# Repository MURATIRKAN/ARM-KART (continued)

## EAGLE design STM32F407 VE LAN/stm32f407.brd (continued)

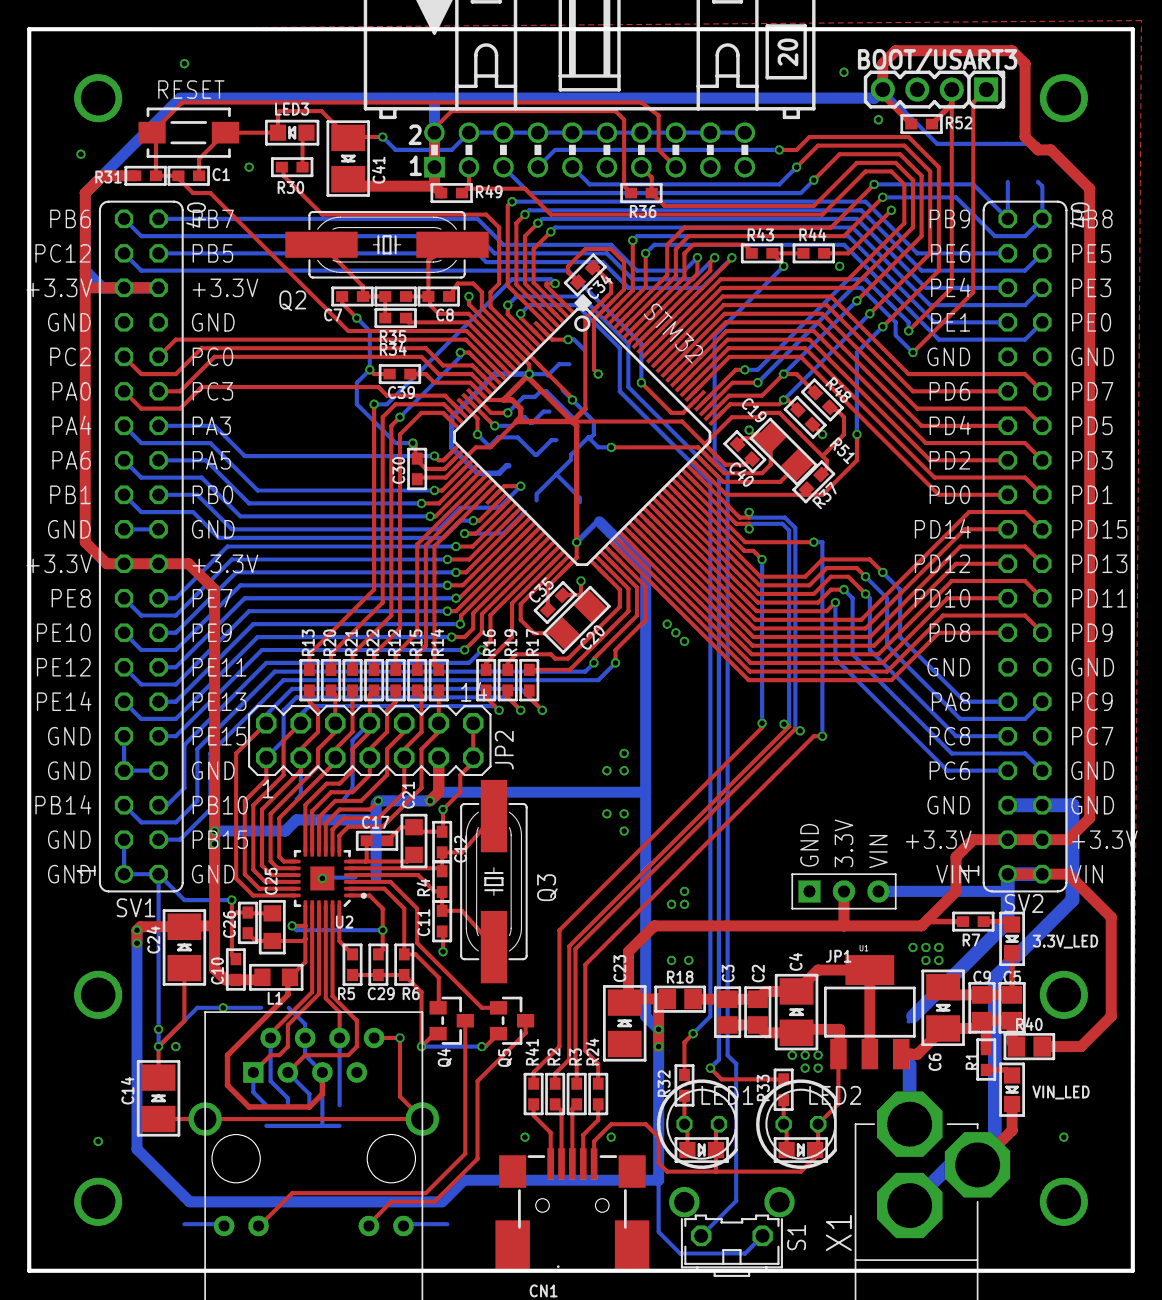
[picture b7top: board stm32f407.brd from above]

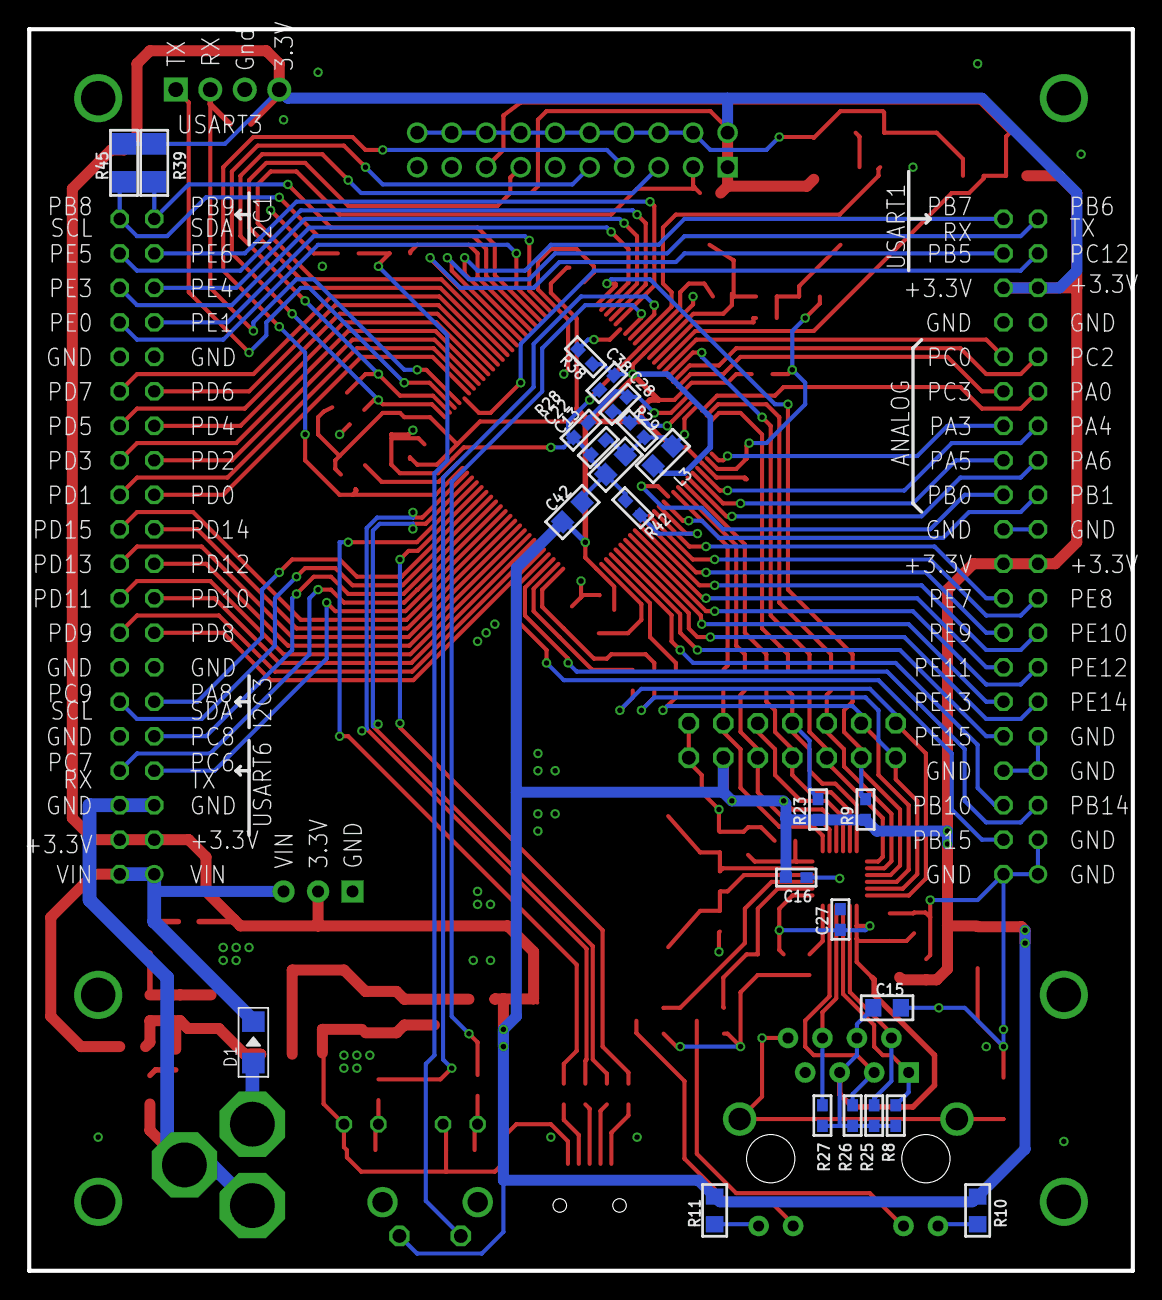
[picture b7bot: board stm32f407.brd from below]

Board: 4 copper layers, 81.3 x 91.4 mm, 119 parts (24 on the bottom side), 134 nets.

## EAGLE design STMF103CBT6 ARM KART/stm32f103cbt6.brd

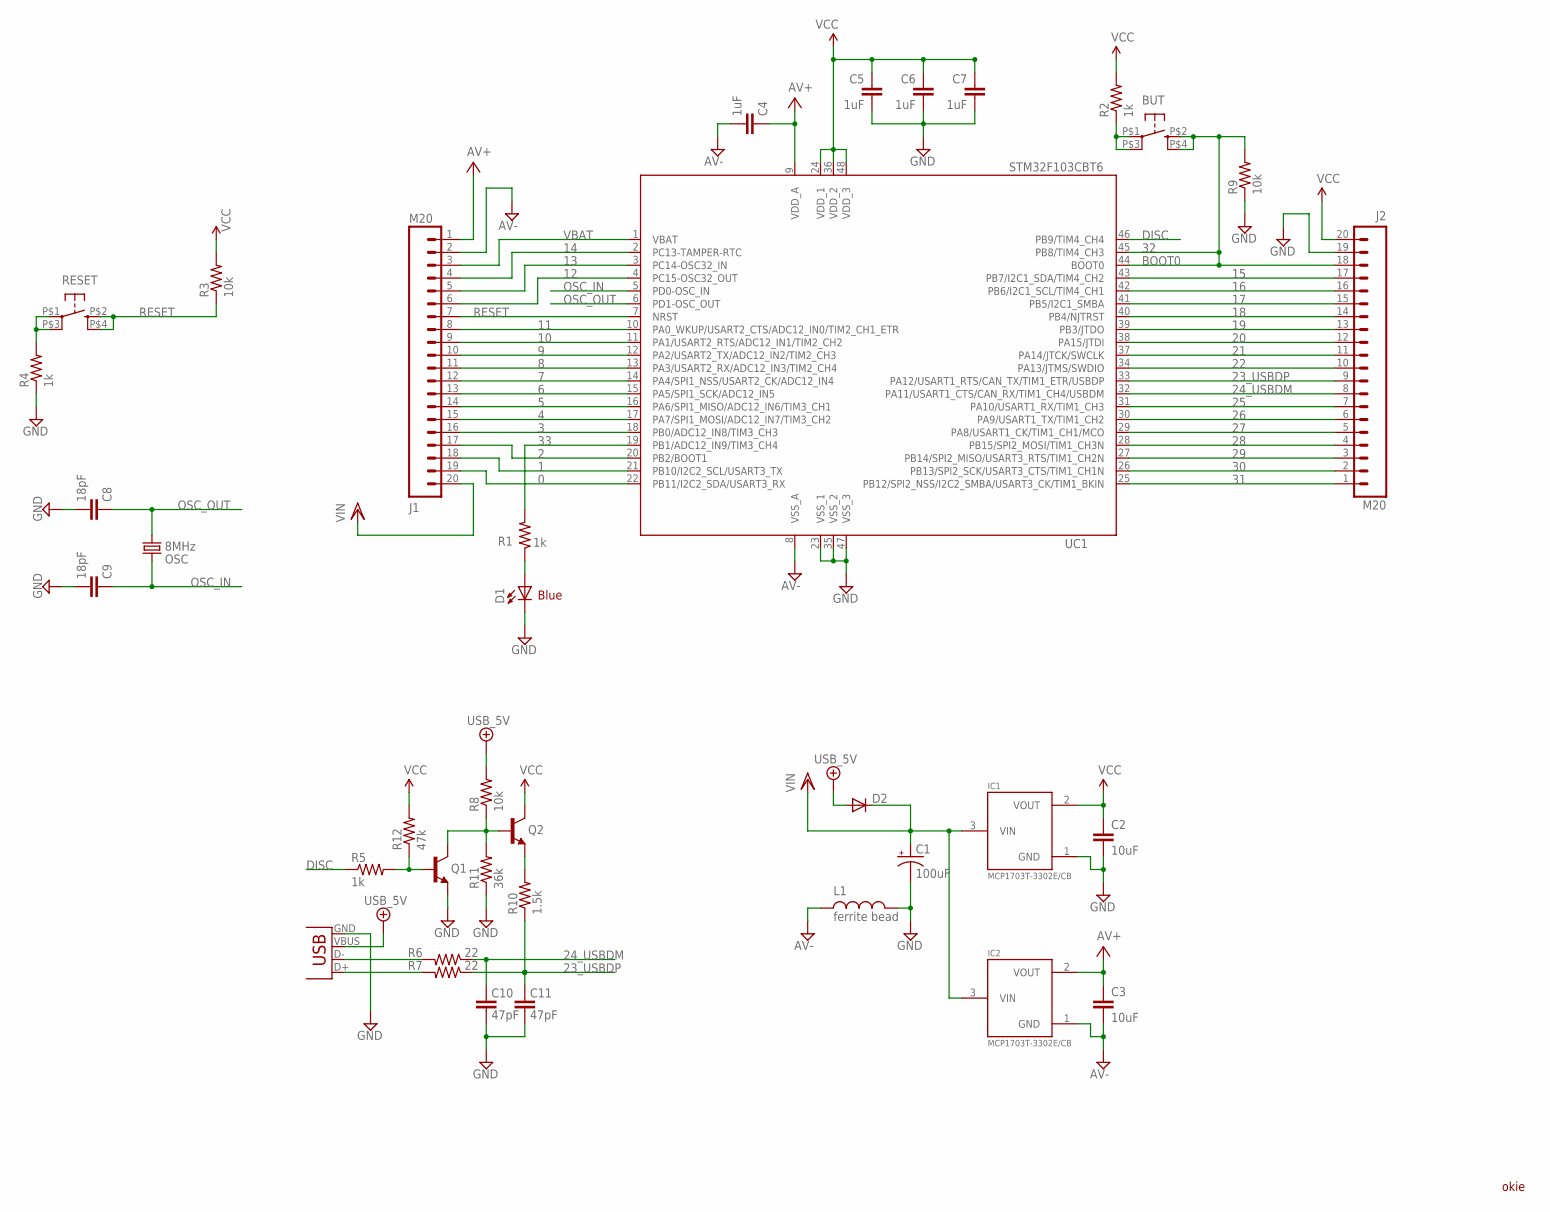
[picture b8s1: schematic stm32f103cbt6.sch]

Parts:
BUT: KMR211GLFS; PUSHBUTTON-KMR241GLFS
C1: 100uF; EIA3216
C2, C3: 10uF; 0805
C4, C5, C6, C7: 1uF; C0402
C8, C9: 18pF; C0402
C10, C11: 47pF; C0402
D1: Blue; LED-1206
D2: DIODESOD; SOD-323
IC1, IC2: MCP1703T-3302E/CB; SOT23
J1, J2: M20; 1X20
L1: ferrite bead; 0603
OSC: 8MHz; CRYSTAL-SMD-5X3
Q1, Q2: NPN-BJT; SOT23
R1, R2, R4, R5: 1k; C0402
R3, R8, R9: 10k; C0402
R6, R7: 22; C0402
R10: 1.5k; C0402
R11: 36k; C0402
R12: 47k; C0402
RESET: KMR211GLFS; PUSHBUTTON-KMR241GLFS
UC1: STM32F103CBT6; LQFP48
X1: USB-MINIB

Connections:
0: J1.19, UC1.22 (PB11/I2C2_SDA/USART3_RX)
1: J1.18, UC1.21 (PB10/I2C2_SCL/USART3_TX)
2: J1.17, UC1.20 (PB2/BOOT1)
3: J1.16, UC1.18 (PB0/ADC12_IN8/TIM3_CH3)
4: J1.15, UC1.17 (PA7/SPI1_MOSI/ADC12_IN7/TIM3_CH2)
5: J1.14, UC1.16 (PA6/SPI1_MISO/ADC12_IN6/TIM3_CH1)
6: J1.13, UC1.15 (PA5/SPI1_SCK/ADC12_IN5)
7: J1.12, UC1.14 (PA4/SPI1_NSS/USART2_CK/ADC12_IN4)
8: J1.11, UC1.13 (PA3/USART2_RX/ADC12_IN3/TIM2_CH4)
9: J1.10, UC1.12 (PA2/USART2_TX/ADC12_IN2/TIM2_CH3)
10: J1.9, UC1.11 (PA1/USART2_RTS/ADC12_IN1/TIM2_CH2)
11: J1.8, UC1.10 (PA0_WKUP/USART2_CTS/ADC12_IN0/TIM2_CH1_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)
12: J1.6, UC1.4 (PC15-OSC32_OUT)
13: J1.5, UC1.3 (PC14-OSC32_IN)
14: J1.4, UC1.2 (PC13-TAMPER-RTC)
15: J2.17, UC1.43 (PB7/I2C1_SDA/TIM4_CH2)
16: J2.16, UC1.42 (PB6/I2C1_SCL/TIM4_CH1)
17: J2.15, UC1.41 (PB5/I2C1_SMBA)
18: J2.14, UC1.40 (PB4/NJTRST)
19: J2.13, UC1.39 (PB3/JTDO)
20: J2.12, UC1.38 (PA15/JTDI)
21: J2.11, UC1.37 (PA14/JTCK/SWCLK)
22: J2.10, UC1.34 (PA13/JTMS/SWDIO)
23_USBDP: C11.2, J2.9, R7.1, R10.1, UC1.33 (PA12/USART1_RTS/CAN_TX/TIM1_ETR/USBDP)
24_USBDM: C10.2, J2.8, R6.1, UC1.32 (PA11/USART1_CTS/CAN_RX/TIM1_CH4/USBDM)
25: J2.7, UC1.31 (PA10/USART1_RX/TIM1_CH3)
26: J2.6, UC1.30 (PA9/USART1_TX/TIM1_CH2)
27: J2.5, UC1.29 (PA8/USART1_CK/TIM1_CH1/MCO)
28: J2.4, UC1.28 (PB15/SPI2_MOSI/TIM1_CH3N)
29: J2.3, UC1.27 (PB14/SPI2_MISO/USART3_RTS/TIM1_CH2N)
30: J2.2, UC1.26 (PB13/SPI2_SCK/USART3_CTS/TIM1_CH1N)
31: J2.1, UC1.25 (PB12/SPI2_NSS/I2C2_SMBA/USART3_CK/TIM1_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)
32: BUT.P$2 (2), BUT.P$4 (4), J2.18, R9.2, UC1.44 (BOOT0), UC1.45 (PB8/TIM4_CH3)
33: R1.2, UC1.19 (PB1/ADC12_IN9/TIM3_CH4)
+5V/2: D2.2 (A), R8.2, X1.VBUS
AV+: C3.1, C4.1, IC2.2 (VOUT), J1.1, UC1.9 (VDD_A)
AV-: C3.2, C4.2, IC2.1 (GND), J1.2, L1.1, UC1.8 (VSS_A)
DGND: C1.C (-), C2.2, C5.2, C6.2, C7.2, C8.2, C9.2, C10.1, C11.1, D1.C, IC1.1 (GND), J2.19, L1.2, Q1.2 (E), R4.1, R9.1, R11.1, UC1.23 (VSS_1), UC1.35 (VSS_2), UC1.47 (VSS_3), X1.GND
DISC: R5.1, UC1.46 (PB9/TIM4_CH4)
unnamed: BUT.P$1 (1), BUT.P$3 (3), R2.1
unnamed: D1.A, R1.1
unnamed: R4.2, RESET.P$1 (1), RESET.P$3 (3)
unnamed: Q2.2 (E), R10.2
unnamed: R6.2, X1.D-
unnamed: R7.2, X1.D+
unnamed: Q1.3 (C), Q2.1 (B), R8.1, R11.2
unnamed: Q1.1 (B), R5.2, R12.1
OSC_IN: C9.1, OSC.3 (2), UC1.5 (PD0-OSC_IN)
OSC_OUT: C8.1, OSC.1, UC1.6 (PD1-OSC_OUT)
RESET: J1.7, R3.1, RESET.P$2 (2), RESET.P$4 (4), UC1.7 (NRST)
VBAT: J1.3, UC1.1 (VBAT)
VCC: C2.1, C5.1, C6.1, C7.1, IC1.2 (VOUT), J2.20, Q2.3 (C), R2.2, R3.2, R12.2, UC1.24 (VDD_1), UC1.36 (VDD_2), UC1.48 (VDD_3)
VIN: C1.A (+), D2.1 (C), IC1.3 (VIN), IC2.3 (VIN), J1.20

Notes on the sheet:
okie
BOOT0
Blue

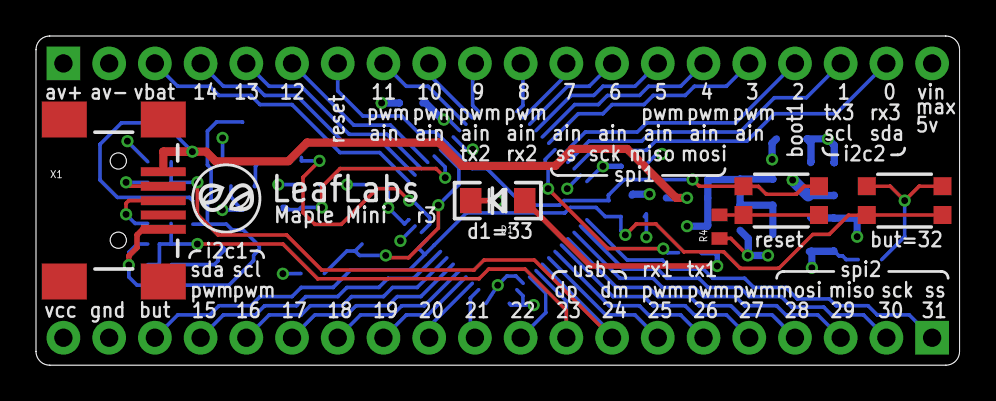
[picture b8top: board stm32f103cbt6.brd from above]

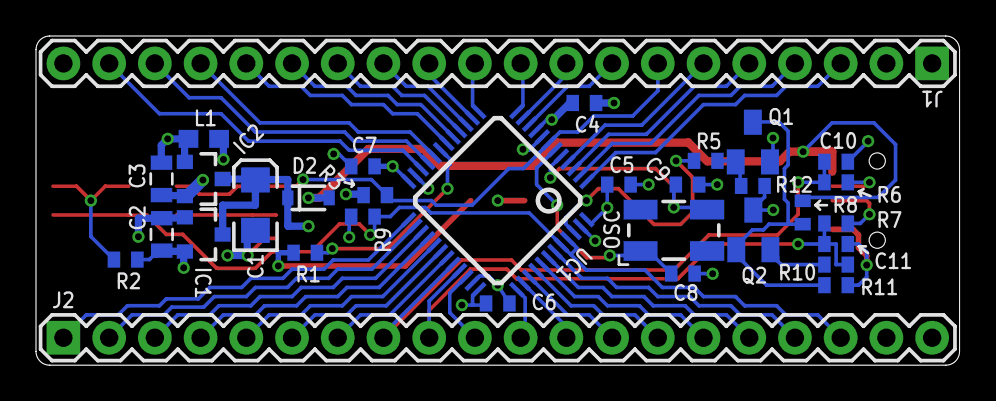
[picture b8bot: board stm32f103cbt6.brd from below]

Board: 2 copper layers, 51.3 x 18.3 mm, 37 parts (32 on the bottom side), 53 nets.

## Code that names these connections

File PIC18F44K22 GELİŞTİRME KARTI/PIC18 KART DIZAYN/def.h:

#ifndef INC_DEF_H
#define INC_DEF_H

#include <p18f44k22.h>
#include <delays.h>
#include <string.h>
#include <stdlib.h>
#include <stdio.h>
#include "init_periph.h"
#include "usart.h"
#include "analog.h"

//////////////////////////////////////////////////////////////////////////////////////////////
//                                                                                          //
//                                  		Prototypes                                		//
//                                                                                          //
//////////////////////////////////////////////////////////////////////////////////////////////

void pre_config(void);
void config(void);
void Interrupt_High(void); 
//void can_proc_message(CAN_MESSAGE *message);
//void init_default_variables(void);

//////////////////////////////////////////////////////////////////////////////////////////////
//                                                                                          //
//                                          Definitions                                     //
//                                                                                          //
//////////////////////////////////////////////////////////////////////////////////////////////

#define ANALOG_CHANNELS 12

//Inputs and outputs

//Analog (user)
#define TRIS_AN0	TRISAbits.TRISA0
#define TRIS_AN1	TRISAbits.TRISA1
#define TRIS_AN2	TRISAbits.TRISA2
#define TRIS_AN3	TRISAbits.TRISA3
#define TRIS_AN4	TRISAbits.TRISA5
#define TRIS_AN5	TRISEbits.TRISE0
#define TRIS_AN6	TRISEbits.TRISE1
#define TRIS_AN7	TRISEbits.TRISE2

//Digital (user)
#define DIO			PORTD
#define TRIS_DIO	TRISD
#define DIO_0		PORTDbits.RD0
#define TRIS_DIO_0	TRISDbits.TRISD0
#define DIO_1		PORTDbits.RD1
#define TRIS_DIO_1	TRISDbits.TRISD1
#define DIO_2		PORTDbits.RD2
#define TRIS_DIO_2	TRISDbits.TRISD2
#define DIO_3		PORTDbits.RD3
#define TRIS_DIO_3	TRISDbits.TRISD3
#define DIO_4		PORTDbits.RD4
#define TRIS_DIO_4	TRISDbits.TRISD4
#define DIO_5		PORTDbits.RD5
#define TRIS_DIO_5	TRISDbits.TRISD5
#define DIO_6		PORTDbits.RD6
#define TRIS_DIO_6	TRISDbits.TRISD6
#define DIO_7		PORTDbits.RD7
#define TRIS_DIO_7	TRISDbits.TRISD7

//Power outputs (user)
#define PWR_0		PORTCbits.RC0
#define TRIS_PWR_0	TRISCbits.TRISC0
#define PWR_1		PORTCbits.RC1
#define TRIS_PWR_1	TRISCbits.TRISC1
#define PWR_2		PORTCbits.RC2
#define TRIS_PWR_2	TRISCbits.TRISC2
#define PWR_3		PORTCbits.RC3
#define TRIS_PWR_3	TRISCbits.TRISC3
#define PWR_4		PORTCbits.RC4
#define TRIS_PWR_4	TRISCbits.TRISC4
#define PWR_5		PORTCbits.RC5
#define TRIS_PWR_5	TRISCbits.TRISC5

//Analog (pre-defined)
#define TRIS_TEMP	TRISBbits.TRISB1
#define TRIS_AMP	TRISBbits.TRISB2
#define TRIS_VOLT1	TRISBbits.TRISB3
#define TRIS_VOLT2	TRISBbits.TRISB4

//Misc.
#define ALIVE		LATAbits.LATA4
#define TRIS_ALIVE	TRISAbits.TRISA4
#define TRIS_RX		TRISCbits.TRISC7
#define TRIS_TX		TRISCbits.TRISC6

#endif

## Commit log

2022-09-24 STM32F401CCT6 ARM KART DİZAYN
    PCB VE ŞEMA.
    KİCAD ELEKTRONIK TASARIM PROGRAMI.
    https://www.kicad.org/
2022-09-24 STM32F042x6 ARM TEMEL KARTI
    NOT:KART PINLERI DEGISTIRILDI.!
2022-09-24 STM32F407 ARM GELISTIRME VE INTERNET KARTI
2022-09-24 STM32F042x6 SERİSİ DEMO KART DİZAYN.
    v.1.01
2022-09-26 STM32F405RGT6 ARM KART
2022-09-28 STM32F765VIT6 EAGLE VE DIP TRACE
    TASARLANIRKEN EAGLE TASARIM PROGRAMI VE DIP TRACE PROGRAMLARI KULLANILDI.
    1.https://diptrace.com/tr/
    2.https://www.autodesk.com/products/eagle/free-download
2022-09-29 STM32F401 ARM KEIL KOD
    ARM KEIL 6.18 DERLEYICI KULLANILDI.
2022-10-01 STM32F765VIT ARM KART V.1.02
    GUNCELLEME 9/1/2022
2022-10-02 STMF103CBT6 MINI ARM GELISTIRME KARTI
2022-10-02 stm32f103cbt6 pcb
2022-10-02 STM32F103 ZAMANLAMA VE LED KONTROL
    DERLEYICI KEIL ARM 6.18.
2022-10-08 STM32F103CBT6 TEMEL ARM KART
    ST MICROELEKTRONICS STM32F103CBT6 ARM - CORTEX M3 İŞLEMCİ
2022-10-08 STM32F103 ARM KEIL 6.18 DERLEYİCİ.
    STM32F103 ZAMANLAMA TEST KOD..
2022-10-08 STM32F103 ZAMANLAMA KODLARI.
    KEIL ARM VERSIYON 6.18
2022-10-08 STM32F042
2022-10-08 STM32F765VIT6 ARM CORTEX M7 DEMO.
2022-10-08 STM32F405RGT6 DEMO KART.KICAD TASARIM PROGRAMI.
2022-10-08 STM32F401 ARM CORTEX-M4 MINI
    STM32F401 ARM CORTEX-M4 MİNİ GELİŞTİRME KARTI
    V.1.02
2022-10-08 STM32F ARM KARTLAR.
2022-10-08 STM32F765VIT6 DEMO ARM KART
2022-10-14 STM32F103CBT6 MINI ARM GELİŞTİRME KARTI.
    V.1.01
    6/10/2022
2022-10-14 STM32F103CBT6 MİNİ ARM_CORTEX M3 GELİŞTİRME KARTI.
2022-10-14 STM32F103CBT6 MİNİ ARM CORTEX-M3 GELİŞTİRME KARTI.
    KART AUTODESK VEYA DIP TRACE İLE TASARLANMIŞTIR.
    V.1.02
2022-10-14 STM32F401 ARM GELİŞTİRME KARTI KICAD.
    KICAD ARM GELİŞTİRME KARTI DEMO.
2022-10-15 stm32f103cbt6 V.1.02
    MİNİ STM32F103CBT6 ARM KART...
2022-10-15 Delete STM32F103CBT6 ARM_KART directory
    DIPTRACE ELEKTRONIK TASARIM PROGRAMI
    STM32F103CBT6 PCB DEVRE TASARIMI..
2022-10-15 STM32F103CBT6:DIPTRACE TASARIM PROGRAMI v.1.02
    NOT:DEVRE USB DEN PROGRAMLANIR.STLINK ADAPTORU İLE.
2022-10-16 stm32f103cbt6 MİNİ ARM KART.(JTAG)
    GÜNCELLEME=JTAG-PROGRAMLAMA SOKETİ EKLENDİ.
    MİNİ JTAG SOKET..
2022-10-16 STM32F103CBT6 ARM GELİŞTİRME KARTI.
    JTAG PORTU VE GÜÇ LEDLERİ EKLENDİ.
2022-10-16 DIPTRACE TASARIM PROGRAMI.
    STM32F103CBT6 ARM-CORTEX M3 GELİŞTİRME KARTI.
    V.1.06 LEDLER VE JTAG SOKET EKLENDİ(MİNİ)
2022-10-17 STM32F103CBT6 DIPTRACE VE EAGLE TASARIM.
    MALZEME LİSTESİ EXCEL,GÜÇ LEDLERİ,MİNİ JTAG EKLENDİ.
    DELİKLER 2mm BOYUTUNDA TASARLANDI.
    V.1.07
2023-01-22 PIC18F44K22 KART
    PIC18F44K22 GELİŞTİRME KARTI..
2023-01-26 STM32F405RGT6V ARM KART
2023-01-26 yapay zeka tanıtımı
2023-01-30 STM32F405RGT6 ARM KART PCB
2023-01-30 STM32F405RGT6 AUTODESK EAGLE
2023-01-31 ARDUINO SICAKLIK VE ISIK TEST
2023-01-31 STM32F407 ARM VE INTERNET
2023-01-31 STM32F103CBT6 MINI ARM KART
    V.1.02
2023-01-31 ARDUINO SICAKLIK_ISIK KOD
2023-02-01 ARDUINO TOSHIBA TBN6612FNG MOTOR SURUCU
2023-02-01 ARDUINO BOSCH BME280 SENSOR
2023-02-01 STM32F405 VE 407 DOKUMAN
2023-02-01 ARDUINO DHT22 SENSOR
2023-02-01 STM32 LM35 VE LCD
2023-02-01 STM32F103 ARM KEIL LCD EKRAN
2023-02-01 STM32F103 AUTODESK EAGLE PCB VE SEMA
2023-02-01 arduıno l298 motor
2023-02-04 PIC18F44K22 KART
    MICRO-C ORNEK
2023-02-04 STMF103CBT6 ARM KART
2023-02-04 MICRO C PIC16 DC18B20 SENSOR
2023-02-07 STM32F405RGT6 ARM GELİŞTİRME KARTI
2023-02-07 PIC18F44K50 VE 45K50 GELİŞTİRME KARTI
2023-02-07 STM32F103CBT6 MINI ARM KART
2023-02-08 STM32F401CCT6 ARM VE ORNEK KiCad 6.0
2023-02-08 STM32F401CB PROTEUS VE KOD
2023-02-08 STM32F401CB KART/ARM KEIL KOD VE PROTEUS
2023-02-08 PIC16F877 MICRO_C LM35 SENSOR
2023-02-08 PIC18F44K22 VEYA PIC18F45K50 KART
    LM35 MICRO_C DERLEYICI
2023-02-08 STM32F407 ARM GELISTIRME VE INTERNET
2023-02-08 STM32F103CBT6 MINI ARM GELISTIRME KARTI
2023-02-08 STM32F401CB ARM GELISTIRME KARTI
2023-02-08 C & PYTHON KİTAP
2023-02-08 BANANA PI ARM BILGISAYAR
2023-02-08 CIZGI IZLEYEN ROBOT TASARIMI SOLIDWORKS
    ARDUINO NANO
2023-02-08 STM32F407 BOSCH BME280 SENSOR
2023-02-08 STM32 KUTUPHANELERI
2023-02-08 STM32F765VIT6 ARM GELISTIRME KARTI
2023-02-08 STM32 ARM KAMERA KEIL ARM DERLEYICI
2023-02-08 STM32 KAMERA
2023-02-08 STM32 KAMERA OV9655 ARM KEIL
2023-02-08 STM32 MICRO PYTHON KODLAR
2023-02-09 STM32F103 DC MOTOR KONTROL ARM KEIL
2023-02-09 ARDUINO HAVA ISTASYONU SOLIDWORKS TASARIM DEMO
2023-02-15 BLDC MOTOR KONTROL DİZAYN
2023-02-15 ARM KEIL STM32F103 STEP MOTOR VE PROTEUS
2023-02-17 MPU6050 PUSULA VE İVME SENSORÜ
2023-02-18 ARDUINO HAVA İSTASYON PROTEUS v8.13
2023-02-18 ARDUINO HAVA İSTASYON-PROTEUS v8.13
2023-02-18 ARDUINO BASINC OLCUM CIHAZI
2023-02-21 PIC18F44K22
2023-02-23 STM32F103CBT6 GELISTIRME KARTI
2023-02-23 PYTHON TERMAL KAMERA MLX90640
2023-02-26 STM32F401CCT6 ARM GELISTIRME KART v.1.01
    KICAD TASARIM PROGRAMI
2023-02-26 STM32F401CCT6 ARM CORTEX M4 GELISTIRME KARTI
    V.1.02
2023-02-26 STM32 ARM BLDC MOTOR KONTROL SİSTEMİ
2023-02-26 ARDUINO NANO CIZGI IZLEYEN ROBOT SOLIDWORKS 2018
2023-02-26 STM32F405RGT6 ARM YAPAY ZEKA KARTI
2023-02-26 STM32F765VIT6 ARM GELSITIRME KARTI
    DEMO VERSIYON
2023-02-26 BEAGLEBONE BLACK I2C BAGLANTI KUTUPHANESI
2023-05-23 MICROCHIP ATSAM51G ARM-32 BIT GELISTIRME KARTI
    REV .1.02
2023-05-23 MICROCHIP ATSAM51G ARM GELİŞTİRME KARTI
    REV 1.2.1
2023-05-23 STM32F405RG ARM VE YAPAY ZEKA KARTI
2023-05-23 STM32F405RG ARM VE YAPAY ZEKA GELİŞTİRME KARTI
    REV 1.00.1
2023-05-23 STM32F407xx ARM CORTEX M4 GELİŞTİRME KARTI
    LOKAL İNTERNET KARTI.
    REV.1.01
2023-05-23 STM32F401 ARM CORTEX M4 KART
    REV.1.5
2023-05-23 MICROCHIP PIC18F44K22 KONTROL KARTI
    REV.1.03
2023-05-24 DIPTRACE MLX90640 TERMAL KAMERA MODÜLÜ ŞEMA
2023-05-24 LM3671-600miliAMPER regulatör
2023-05-24 ADAFRUIT TRINKET KART SERİSİ
2023-05-30 STM32F103CB ARM GELİŞTİRME KARTI
2023-05-30 NXP LPC1768 MCU GELİŞTİRME KARTI
2023-05-30 NXP LPC1343 GELİŞTİRME KARTI
2023-05-30 MICROCHIP ENJ424J600 NETWORK KARTI
2023-06-02 PIC24FJ256GB106 VE LAN GELİŞTİRME KARTI v.1.03
2023-06-02 PIC24FJ256GB106 16-BIT MCU VE LAN KARTI
    VERSIYON 1.1.2
2023-06-02 ENC424J600 NETWORK(LAN 10/100 MEGABIT) KARTI
    V.1.01
2023-06-02 STM32F407VE AR GELİŞTİRME VE NETWORK KARTI
2023-06-02 ENC424J600 LAN KARTI 10/100 MEGABIT
2023-06-02 MICROCHIP PIC18F44K22 GELİŞTİRME KARTI
    v.1.2
2023-06-02 ARDUINO STEREO RADYO + 35mW AM-FI KARTI
2023-06-03 PIC18F44K22 VE PIC18F45K50 GELİŞTİRME KARTI
    v.1.2
2023-06-03 CNC MAKİNESİ KONTROL KARTI
    A4988 STEP MOTOR 2x3 TOPLAM 6 AMPER,ATMEGA 328P MCU+ USB
2023-06-04 ARM CORTEX-M4 STM32F405RG GELİŞTİRME KARTI
    v.1.2 devre şeması ve DATASHEET.
    DEMO VERSİYONDUR.
2023-06-04 MICROCHIP ATSAMD51G ARM CORTEX M4 KART
    rev.1.00
2023-06-04 CNC MAKİNESİ KONTROL KARTI ATMEGA328P MCU
    A4988 STEP MOTOR 3-EKSEN 2 AMPER
2023-06-04 PIC18F44K22 VEYA PIC18F45K50 GELİŞTİRME KARTI.
2023-06-04 CNC MAKİNE KONTROL KARTI ARMEGA328P v.1.02
    demo kart 3-EKSEN 2 AMPER A4988 STEP MOTOR
2023-06-05 TEMEL ROBOT MODEL SOLIDWORK 2018
2023-06-05 STM32F407VE ARM GELİŞTİRME KARTI PCB
2023-06-05 MSP430 GELİŞTİRME KARTI
2023-06-05 STM32F030F4x ARM CORTEX-M0 DEVRE ŞEMASI PDF
    DİĞER ELEKTRONİK PARÇALAR.
2023-06-05 PARALLAX BASIC STAMP 2 DEVRE
2023-06-06 STM32F405RGT6 ARM GELİŞTİRME KARTI
    REGULATOR AMS1117 0.8 AMPER TOPLAM AKIM
2023-06-06 CNC KONTROL KARTI PCB A4988 3-EKSEN 2 AMPER
    ücretli demo versiyondur.
2023-06-06 CNC MAKİNESİ KONTROL KARTI A4988 3-EKSEN 2AMPER
    REV.1.03
2023-06-07 CNC MAKİNESİ KONTROL KARTI 2 AMPER STEP MOTOR
    REV.1.00
2023-06-07 TEXAS INSTRUMENTS DRV8833 DC MOTOR KONTROL PCB
2023-06-08 TI DRV8833 DC VE STEP MOTOR SÜRÜCÜ KARTI
2023-06-08 DRV8833: 2 DC-1 STEP MOTOR SÜRÜCÜ KARTI
2023-06-08 MICROCHIP HASSAS SICAKLIK SENSOR MCP9808
    SENSOR KARTI
2023-06-08 DRV8313 PYTHON BLCD MOTOR SÜRÜCÜSÜ ÖRNEK KOD
2023-06-08 TI DRV8871 TEK DC MOTOR 3.6 AMPER MOTOR SÜRÜCÜSÜ
2023-06-08 TI DRV8871 2-3.6 AMPER TEK DC MOTOR SÜRÜCÜSÜ
2023-06-09 MICROCHIP PIC18F45K50 GELİŞTİRME KARTI
    REV.1.02 SATILIK:760 TL
2023-06-11 PIC18F45K50 GELİŞTİRME KARTI(rev.1.02)
2023-06-11 ATSAMD51G ARM CORTEX M4 KART
2023-06-12 NETWORK(LAN) ENC424J600 10/100 MEGABIT
    rev.1.03
2023-06-12 MC33886 DC VE SELENOID MOTOR KONTROL KARTI
    ŞEMA PDF.
2023-06-12 ATMEL ATSAM21G ARM CORTEX KART
2023-06-12 ATSAM21G ARM CORTEX GELİŞTİRME KARTI
    rev.1.02
2023-06-13 NETWORK KART (ENC424J600 10/100)
    rev.1.02
2023-06-13 ÖN MUHASEBE 2.3.21 GÜNCELLEME.(13/06/2023)
    PRO VE LITE VERSİYON OLARAK.
2023-06-13 STM32F405RGT6 ARM-CORTEX M4 DEVRE ŞEMA v.1.02
2023-06-13 STM32F407VE ARM KART
    BU KART SATILIKTIR. REV.1.01
2023-06-14 ENJ424J600 NETWORK TASARIM
    REV.1.02
2023-06-16 TEXAS INSTRUMENTS DRV8833 MOTOR SÜRÜCÜ
    EAGLE ŞEMA VE PCB.
2023-06-17 ATMEL ATTINY85 MCU MİKRO-KART rev:1.00
2023-06-17 ATTINY85-PCB rev.1.01
2023-06-18 PIC24FJ256GB106_16-BIT MCU VE LAN
    rev.1.01
2023-06-18 PIC18F45K50 VEYA PIC18F44K22 KART
    REV.1.01
2023-07-13 PIC18F44K22 VEYA PIC18F45K50 KART
    REV.1.01
2023-10-30 STM32F103CBT6 ARM-KART DİZAYN
    ST MICROELEKTRONICS
2023-10-30 PIC24 + NETWORK KART PIC24FJ256GB106 16-BIT
2023-10-30 AT91SAM MICROCHIUP ARC-LINUX KART
    ARC LINUX MICROCHIP ARM-KART
2023-10-30 PIC16F1938 GELİŞTİRME KARTI 8-BIT v1.01
2023-11-01 APOLLO 3 ARM-CORTEX M4 MCU DİZAYN+ PCB
2023-11-18 MODEL-DEMO
2023-11-18 PROTEUS 8.13 ARDUINO HAVA İSTASYONU
2023-11-27 RASPBERRY PI 2040 DEMO :REV.1.00
    ORNEK RASPBERRY PI 2040 DEVRE TASARIMI
2023-11-27 RASPBERRY PI 2040 ÖRNEK DEVRE
    rev:1.00
2023-11-27 RASPBERRY PI 2040 ÖRNEK TASARIM: REV.1.01
2024-01-22 STM32F407ZET6 ARM GELISTIRME KARTI REV.E VE F
2024-02-02 ALLWINNER A20 ARM LINUX ŞEMA
    REV.B
2024-02-02 ALLWINNER A33 ARM CPU ANDROID TABLET
    REV. VE B
2024-02-02 TEXAS INSTRUMENTS AM3352 ARM LINUX SİSTEM
    REV A ..
2024-02-03 AUTODESK EAGLE ARM BILGISAYAR ANDROID-LINUX
    REV/- A VE C
2024-02-03 PC RESIM ALLWINNER H3
2024-02-06 ANDROID VE LINUX ONBOARD BİLGİSAYAR(MURAT IRKAN)
    REV A VE B
2024-02-19 ST MICROELEKTRONICS ROBOT SİSTEMLERİ PDF
2024-02-19 ROBOT ARABA TASARIM SOLIDWORKS 2018
2024-02-21 NXP İ.MX233 MPU TASARIM rev.e
2024-02-21 CİZGİ İZLEYEN ROBOT SOLIDWORKS 2018
2024-02-21 RAZER OYUNCU MOUSE DEATH ADDER V2 PRO
    SOLIDWORKS 2018
2024-03-03 ALLWINNER H3 LINUX-ANDROID ONBOARD BİLGİSAYAR
    REVİZYON C. v.1.01
2024-03-07 ALLWINNER A64 LINUX SERVER-PC
    REV.A VE REV.B
2024-03-07 ALWINNER A64 LINUX SERVER VE EKİPMAN
    REV.A VE B
2024-03-08 AUTODESK EAGLE ALLWINNER A13 MINI-PC
    REV.C
2024-03-08 A13 DATASHEET-BİLGİ DÖKÜMAN
2024-04-01 NXP-IM233 SİSTEM TASARIM
2024-04-01 ALLWINNER H3 ARM BİLGİSAYAR TASARIM
    LINUX VE ANDROID SİSTEM
2024-04-01 PIC32 32-BIT KONTROL KARTI AUTODESK EAGLE
    REV.1.1
2024-04-06 Create INTEL-LGA1151 PLATFORM
2024-04-06 INTEL LGA1151 PLATFORM
2024-04-06 NVIDIA RTX3080 10GIGABYTE GRAFİK KART DEVRES
2024-04-06 RTX3080 10GIGABYTE
2024-04-06 AMD RX580 8-GIGABYTE
    GIGABYTE AURUS GRAFİK KART
2024-04-06 GIGABYTE-NVIDIA RX3070 8GIGABYTE GRAFİK KART
2024-04-24 ARM OYUN KONSOL PROJESİ
    MURAT IRKAN 2023 REV.B
    AÇIK KAYNAK DONANIM PROJESİ
2024-05-04 ALLWIINER A20 LINUX PC-PCB+ŞEMA REV.A
2024-05-04 ALLWINNER A20 ARM BİLGİSAYAR DEVRE ŞEMASI +PCB
    REV.A VE B
2024-05-10 ST MICROELECTRONICS STM32F407ZET6-PCB REV.C
    STM32F407ZET6 DIPTRACE PCB TASARIM + 3D TASARIM
2024-05-29 A20-PYTHON LEDYAK
2024-06-05 i.mx233 MPU NANO KART
    REV.A
